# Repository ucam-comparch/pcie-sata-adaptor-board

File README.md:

This is a printed circuit board to breakout an 8-lane PCI Express socket into
8x SATA channels, which we have used with Terasic DE4 FPGA boards.

THIS IS NOT A SATA CONTROLLER, it merely uses SATA sockets for the physical
connections as the sockets and cables are cheap, and have good signal integrity.
What you put down the PCIe lanes is up to your FPGA configuration.

Images (the first version with a few hand bugfixes):

The design was created using Eagle PCB, but the gerber files should be
usable even if you don't have Eagle.

The 4-layer board was fabricated by rak.co.uk using a standard-ish stackup:  
0.2mm double sided  
2 pre-pregs (0.15mm)  
0.8mm unclad board  
2 pre-pregs (0.15mm)  
0.2mm double sided  
Total 1.5-1.6mm  

They don't provide controlled impedance boards but our design is sized to
have the correct impedances according to this stackup.

In addition ports are provided for:  
SATA power (3.3V and 12V)  
Altera USB Blaster-compatible JTAG port  

Since we couldn't source SATA power connectors without data, the data part
of the SATA power connector is connected to some I/Os on the PCIe connector. 
This can be used for low-speed signalling from the FPGA.

If you connect a USB Blaster to the JTAG port you need to fit components to
VREF_SRC to supply the correct VREF.  The DE4 uses 2.5V - we fit resistors
68R from 3V3 to VREF and 220R from VREF to ground.

R1/R2/R3 provide access to the unused lines on the JTAG cable, or means to
ground them to reduce noise.

Computer Architecture Group, University of Cambridge Computer Laboratory  
May 2013  
http://www.cl.cam.ac.uk/research/comparch/  

Copyright (c) 2013, Simon Moore  
All rights reserved.  

Redistribution and use in source and binary forms, with or without
modification, are permitted provided that the following conditions are met:

 1. Redistributions of source code must retain the above copyright notice, this
    list of conditions and the following disclaimer.

 2. Redistributions in binary form must reproduce the above copyright
    notice, this list of conditions and the following disclaimer in the
    documentation and/or other materials provided with the distribution.

THIS SOFTWARE IS PROVIDED BY THE COPYRIGHT HOLDERS AND CONTRIBUTORS "AS IS"
AND ANY EXPRESS OR IMPLIED WARRANTIES, INCLUDING, BUT NOT LIMITED TO,
THE IMPLIED WARRANTIES OF MERCHANTABILITY AND FITNESS FOR A PARTICULAR
PURPOSE ARE DISCLAIMED.  IN NO EVENT SHALL THE COPYRIGHT HOLDER OR
CONTRIBUTORS BE LIABLE FOR ANY DIRECT, INDIRECT, INCIDENTAL, SPECIAL,
EXEMPLARY, OR CONSEQUENTIAL DAMAGES (INCLUDING, BUT NOT LIMITED TO,
PROCUREMENT OF SUBSTITUTE GOODS OR SERVICES; LOSS OF USE, DATA, OR
PROFITS; OR BUSINESS INTERRUPTION) HOWEVER CAUSED AND ON ANY THEORY OF
LIABILITY, WHETHER IN CONTRACT, STRICT LIABILITY, OR TORT (INCLUDING
NEGLIGENCE OR OTHERWISE) ARISING IN ANY WAY OUT OF THE USE OF THIS
SOFTWARE, EVEN IF ADVISED OF THE POSSIBILITY OF SUCH DAMAGE.

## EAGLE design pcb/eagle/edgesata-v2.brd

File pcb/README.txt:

File extensions:
Eagle schematic: .sch
Eagle board: .brd
Eagle library: .lbr

Gerber layers:
.crc: component side solder cream frame
.plc: component side silkscreen
.stc: component side solder mask
.cmp: component side copper
.ly2: inner layer copper (layer 2)
.l15: inner layer copper (layer 15)
.sol: solder side copper
.sts: solder side solder mask
.pls: solder side silkscreen
.crs: solder side solder cream frame

Drill files:
.drd: Excellon drill file
.dri: Drill station info file

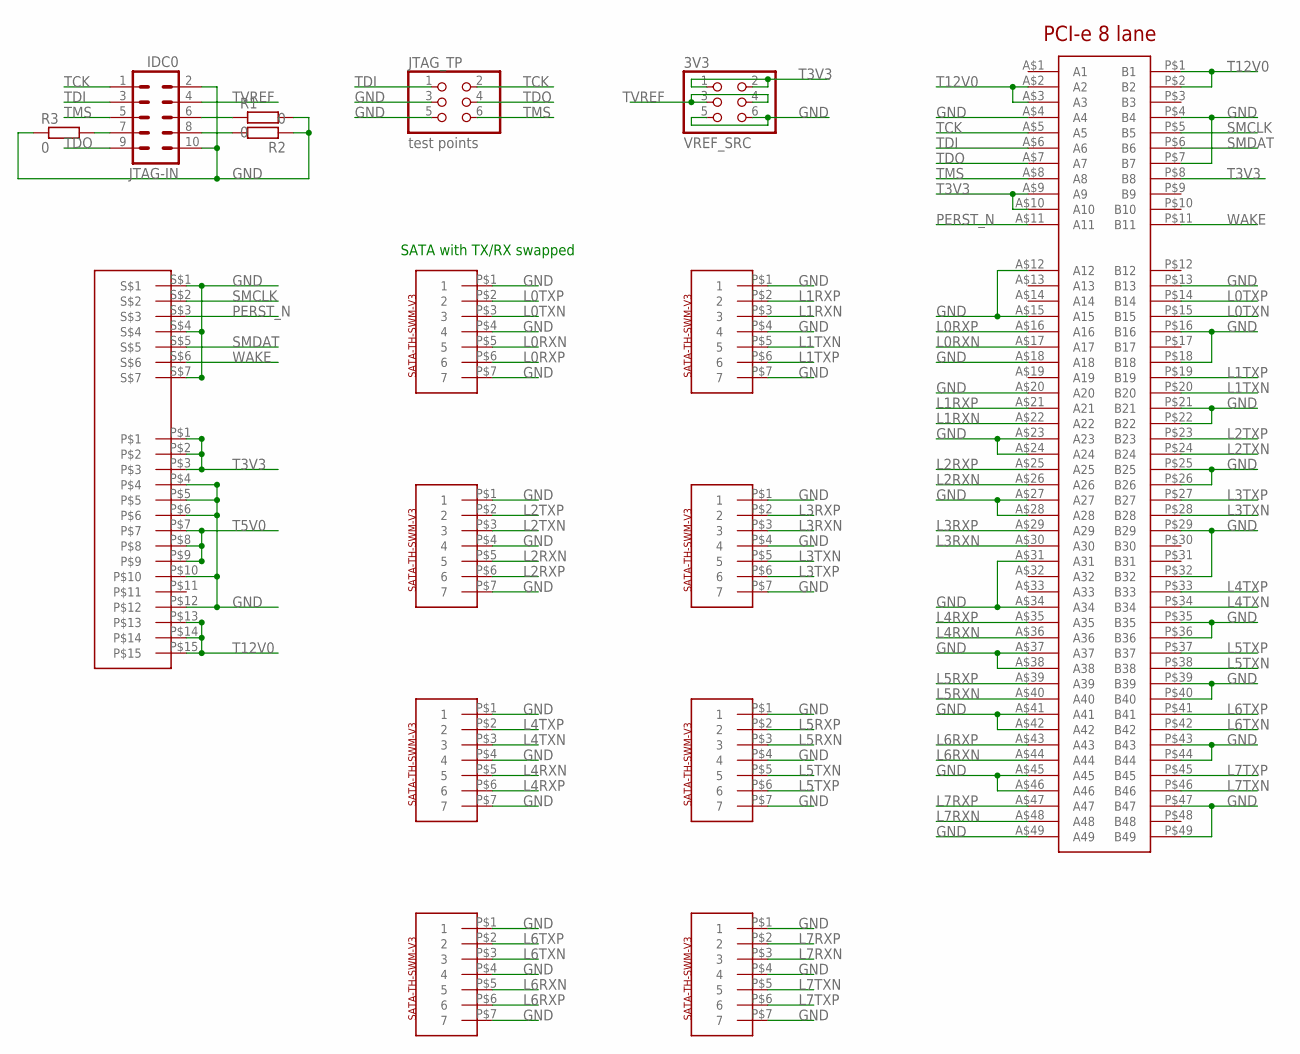
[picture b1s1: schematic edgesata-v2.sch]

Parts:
3V3: VREF_SRC; 2X03
JTAG-IN: IDC0; MA05-2
JTAG_TP: test points; 2X03
LANE0, LANE1, LANE2, LANE3, LANE4, LANE5, LANE6, LANE7: SATA-TH-SWM-V3
R1, R2, R3: 0; R0805W
U$1: SATA-POWER-V1
U$8: PCIE-EDGE-8LANE-V1

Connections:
GND: 3V3.5, 3V3.6, JTAG-IN.2, JTAG-IN.10, JTAG_TP.3, JTAG_TP.5, LANE0.P$1 (1), LANE0.P$4 (4), LANE0.P$7 (7), LANE1.P$1 (1), LANE1.P$4 (4), LANE1.P$7 (7), LANE2.P$1 (1), LANE2.P$4 (4), LANE2.P$7 (7), LANE3.P$1 (1), LANE3.P$4 (4), LANE3.P$7 (7), LANE4.P$1 (1), LANE4.P$4 (4), LANE4.P$7 (7), LANE5.P$1 (1), LANE5.P$4 (4), LANE5.P$7 (7), LANE6.P$1 (1), LANE6.P$4 (4), LANE6.P$7 (7), LANE7.P$1 (1), LANE7.P$4 (4), LANE7.P$7 (7), R1.2, R2.1, R3.1, U$1.P$4, U$1.P$5, U$1.P$6, U$1.P$10, U$1.P$12, U$1.S$1, U$1.S$4, U$1.S$7, U$8.A$4 (A4), U$8.A$12 (A12), U$8.A$15 (A15), U$8.A$18 (A18), U$8.A$20 (A20), U$8.A$23 (A23), U$8.A$24 (A24), U$8.A$27 (A27), U$8.A$28 (A28), U$8.A$31 (A31), U$8.A$34 (A34), U$8.A$37 (A37), U$8.A$38 (A38), U$8.A$41 (A41), U$8.A$42 (A42), U$8.A$45 (A45), U$8.A$46 (A46), U$8.A$49 (A49), U$8.P$4 (B4), U$8.P$7 (B7), U$8.P$13 (B13), U$8.P$16 (B16), U$8.P$18 (B18), U$8.P$21 (B21), U$8.P$22 (B22), U$8.P$25 (B25), U$8.P$26 (B26), U$8.P$29 (B29), U$8.P$32 (B32), U$8.P$35 (B35), U$8.P$36 (B36), U$8.P$39 (B39), U$8.P$40 (B40), U$8.P$43 (B43), U$8.P$44 (B44), U$8.P$47 (B47), U$8.P$49 (B49)
L0RXN: LANE0.P$5 (5), U$8.A$17 (A17)
L0RXP: LANE0.P$6 (6), U$8.A$16 (A16)
L0TXN: LANE0.P$3 (3), U$8.P$15 (B15)
L0TXP: LANE0.P$2 (2), U$8.P$14 (B14)
L1RXN: LANE1.P$3 (3), U$8.A$22 (A22)
L1RXP: LANE1.P$2 (2), U$8.A$21 (A21)
L1TXN: LANE1.P$5 (5), U$8.P$20 (B20)
L1TXP: LANE1.P$6 (6), U$8.P$19 (B19)
L2RXN: LANE2.P$5 (5), U$8.A$26 (A26)
L2RXP: LANE2.P$6 (6), U$8.A$25 (A25)
L2TXN: LANE2.P$3 (3), U$8.P$24 (B24)
L2TXP: LANE2.P$2 (2), U$8.P$23 (B23)
L3RXN: LANE3.P$3 (3), U$8.A$30 (A30)
L3RXP: LANE3.P$2 (2), U$8.A$29 (A29)
L3TXN: LANE3.P$5 (5), U$8.P$28 (B28)
L3TXP: LANE3.P$6 (6), U$8.P$27 (B27)
L4RXN: LANE4.P$5 (5), U$8.A$36 (A36)
L4RXP: LANE4.P$6 (6), U$8.A$35 (A35)
L4TXN: LANE4.P$3 (3), U$8.P$34 (B34)
L4TXP: LANE4.P$2 (2), U$8.P$33 (B33)
L5RXN: LANE5.P$3 (3), U$8.A$40 (A40)
L5RXP: LANE5.P$2 (2), U$8.A$39 (A39)
L5TXN: LANE5.P$5 (5), U$8.P$38 (B38)
L5TXP: LANE5.P$6 (6), U$8.P$37 (B37)
L6RXN: LANE6.P$5 (5), U$8.A$44 (A44)
L6RXP: LANE6.P$6 (6), U$8.A$43 (A43)
L6TXN: LANE6.P$3 (3), U$8.P$42 (B42)
L6TXP: LANE6.P$2 (2), U$8.P$41 (B41)
L7RXN: LANE7.P$3 (3), U$8.A$48 (A48)
L7RXP: LANE7.P$2 (2), U$8.A$47 (A47)
L7TXN: LANE7.P$5 (5), U$8.P$46 (B46)
L7TXP: LANE7.P$6 (6), U$8.P$45 (B45)
unnamed: JTAG-IN.7, R3.2
unnamed: JTAG-IN.6, R1.1
unnamed: JTAG-IN.8, R2.2
PERST_N: U$1.S$3, U$8.A$11 (A11)
SMCLK: U$1.S$2, U$8.P$5 (B5)
SMDAT: U$1.S$5, U$8.P$6 (B6)
T3V3: 3V3.1, 3V3.2, U$1.P$1, U$1.P$2, U$1.P$3, U$8.A$9 (A9), U$8.A$10 (A10), U$8.P$8 (B8)
T5V0: U$1.P$7, U$1.P$8, U$1.P$9
T12V0: U$1.P$13, U$1.P$14, U$1.P$15, U$8.A$2 (A2), U$8.A$3 (A3), U$8.P$1 (B1), U$8.P$2 (B2)
TCK: JTAG-IN.1, JTAG_TP.2, U$8.A$5 (A5)
TDI: JTAG-IN.3, JTAG_TP.1, U$8.A$6 (A6)
TDO: JTAG-IN.9, JTAG_TP.4, U$8.A$7 (A7)
TMS: JTAG-IN.5, JTAG_TP.6, U$8.A$8 (A8)
TVREF: 3V3.3, 3V3.4, JTAG-IN.4
WAKE: U$1.S$6, U$8.P$11 (B11)

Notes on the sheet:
SATA with TX/RX swapped

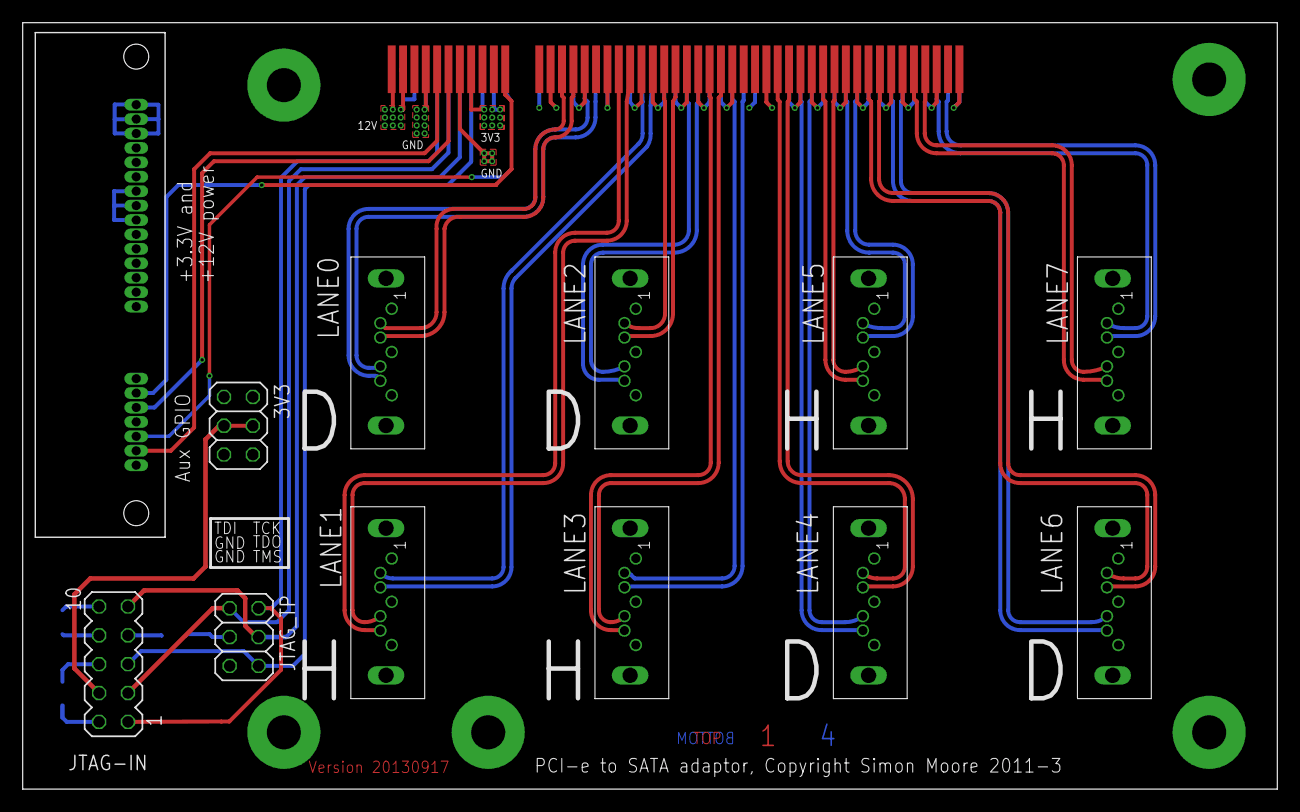
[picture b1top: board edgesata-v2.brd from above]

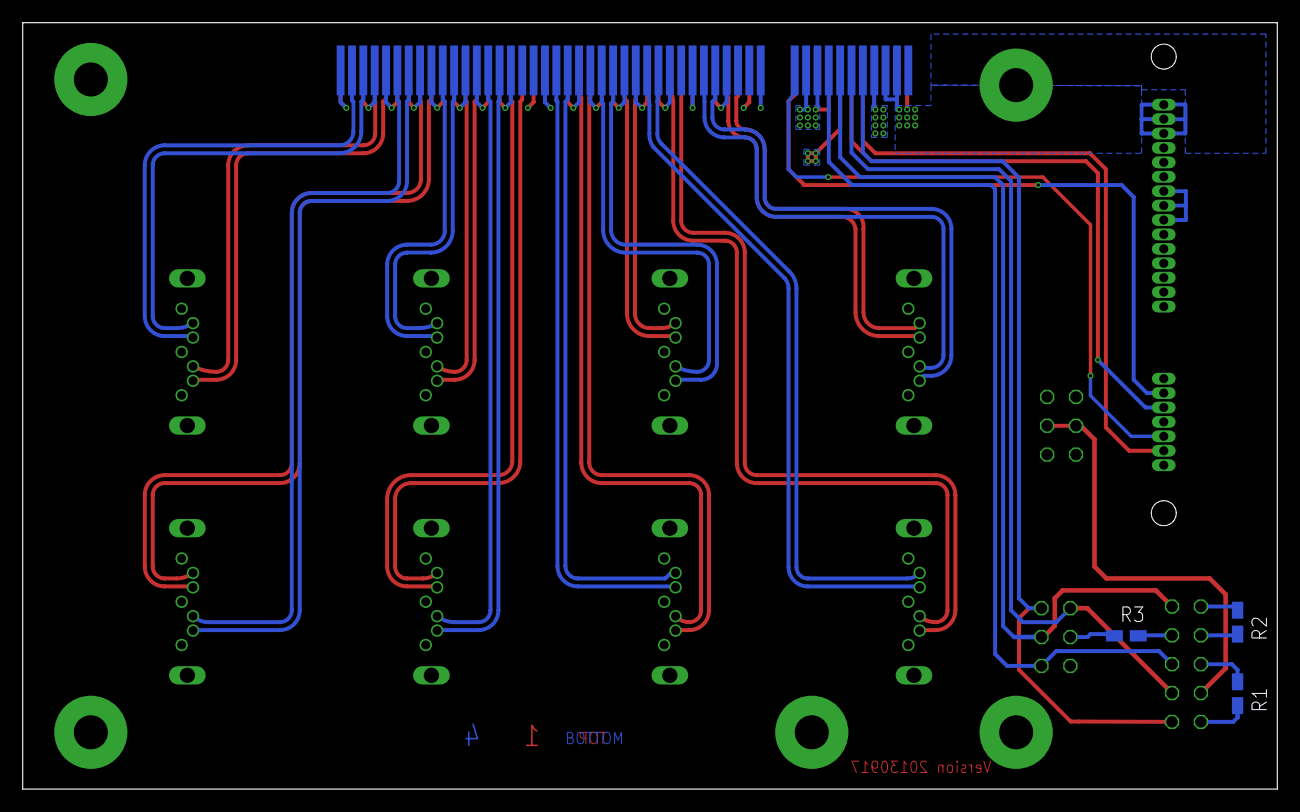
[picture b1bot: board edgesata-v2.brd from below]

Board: 4 copper layers, 110.5 x 67.5 mm, 16 parts (3 on the bottom side), 48 nets.

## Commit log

2013-05-20 Import designs for fabricated board, version 20110809. Bugs currently remaining: USB Blaster JTAG TDI/TDO crossed 4th aux GPIO is connected to PRSNT1# board detect line, not PERST# GPIO
2013-05-20 Split up files into eagle/gerber/drill directories
2013-05-21 Bug fix version - fix problems with crossed JTAG lines and incorrect 4th aux GPIO pins. Not yet tested by fabrication.
2013-05-21 Tidy readme, add links to images
2013-05-21 Generate drill files for new revision of board
2013-09-17 Fix unrouted net to JTAG pulldown resistor R1. Not yet fabrication tested.

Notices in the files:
pcb/eagle/edgesata-v2.brd:
PCI-e to SATA adaptor, Copyright Simon Moore 2011-3
